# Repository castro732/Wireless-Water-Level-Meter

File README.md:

# Wireless Water Level Meter

## Description

System for measuring the water level in a tank using a current loop (4 mA to 20 mA) wirelessly.

The system consists of 2 modules, a local module and a remote module.
	The local module reads the level of water and transmits it to the remote module (using nRF24L0).
	The remote receives the data and displays it using 5 LEDs, corresponding to the 5 levels of water, from empty to full.

## Features
- Wireless, using nRF24L0.
- Programmed via Arduino using an Atmega328P.
- LEDs indicating the level of water in both modules (local and remote).
- Powered with 5V via screw terminals.
- Programming headers (serial) to facilitate the reprogramming of the microcontrollers.
	- Programs using an Arduino.

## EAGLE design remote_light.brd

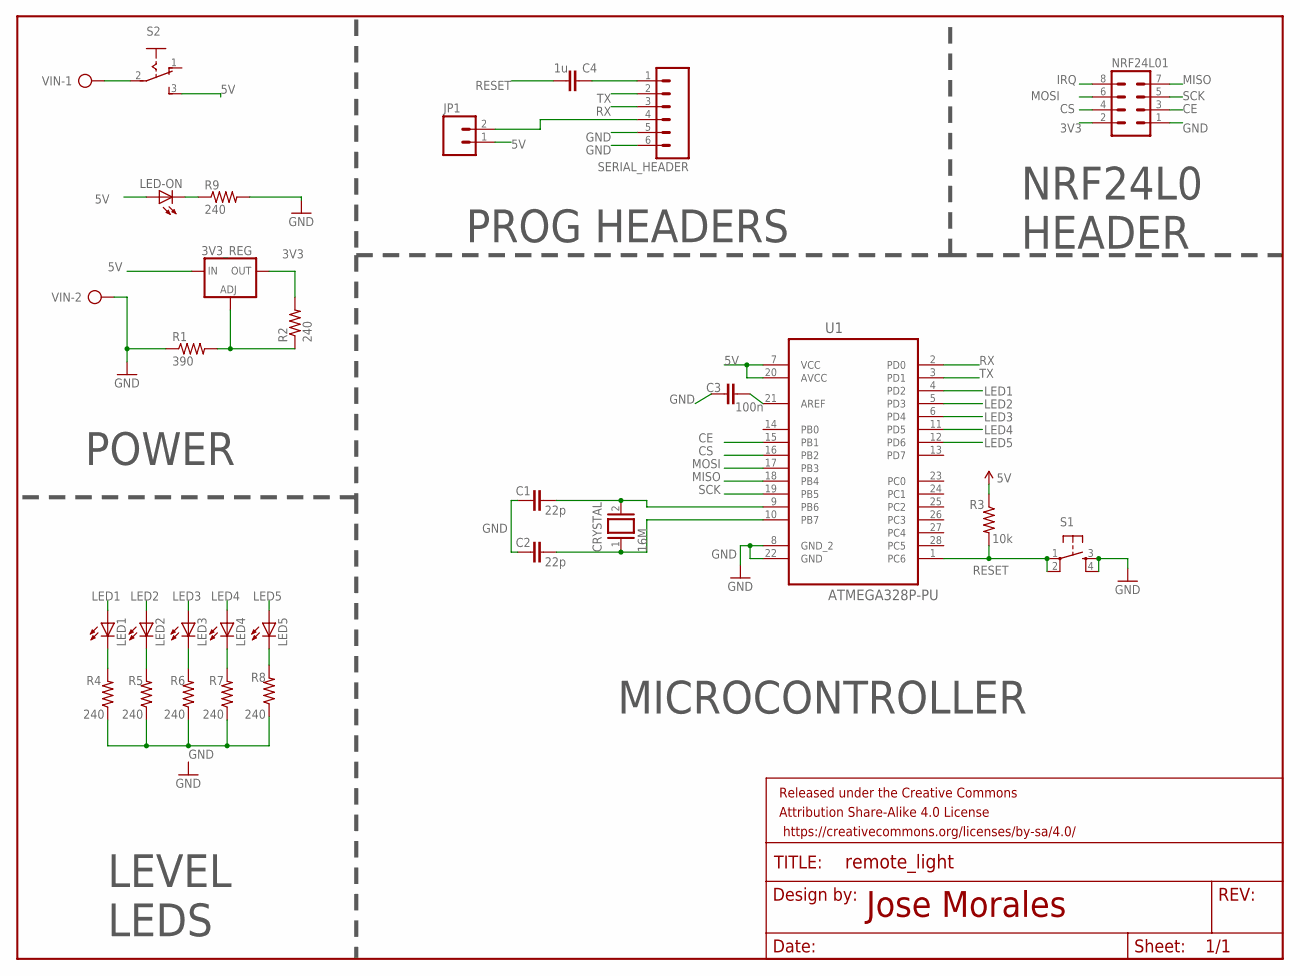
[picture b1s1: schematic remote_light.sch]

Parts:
C1, C2: 22p; C050-025X075
C3: 100n; C050-025X075
C4: 1u; C050-025X075
CRYSTAL: 16M; QS
FRAME11: FRAME-LETTER; CREATIVE_COMMONS
JP1: M02LOCK; 1X02_LOCK
LED1, LED2, LED3, LED4, LED5: LED5MM
LED-ON: LED5MM
LM317: 3V3_REG; 317TS
NRF24L01: MA04-2
R1: 390; 0207/12
R2, R4, R5, R6, R7, R8, R9: 240; 0207/12
R3: 10k; 0207/12
S1: TAC_SWITCHPTH; TACTILE-PTH
S2: 255SB
SERIAL_HEADER: M06POLAR; MOLEX-1X6
U1: ATMEGA328P-PU; DIP254P762X457-28
VIN: AK300/2

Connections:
3V3: LM317.2 (OUT), NRF24L01.2, R2.2
5V: JP1.1, LED-ON.A, LM317.3 (IN), R3.1, S2.3 (S), U1.7 (VCC), U1.20 (AVCC)
CE: NRF24L01.3, U1.15 (PB1)
CS: NRF24L01.4, U1.16 (PB2)
GND: C1.2, C2.2, C3.2, NRF24L01.1, R1.1, R4.1, R5.1, R6.1, R7.1, R8.1, R9.2, S1.3, S1.4, SERIAL_HEADER.5, SERIAL_HEADER.6, U1.8 (GND_2), U1.22 (GND), VIN.2
IRQ: NRF24L01.8
LED1: LED1.A, U1.4 (PD2)
LED2: LED2.A, U1.5 (PD3)
LED3: LED3.A, U1.6 (PD4)
LED4: LED4.A, U1.11 (PD5)
LED5: LED5.A, U1.12 (PD6)
MISO: NRF24L01.7, U1.18 (PB4)
MOSI: NRF24L01.6, U1.17 (PB3)
unnamed: LM317.1 (ADJ), R1.2, R2.1
unnamed: C1.1, CRYSTAL.2, U1.9 (PB6)
unnamed: LED1.K (C), R4.2
unnamed: LED-ON.K (C), R9.1
unnamed: C2.1, CRYSTAL.1, U1.10 (PB7)
unnamed: LED2.K (C), R5.2
unnamed: LED3.K (C), R6.2
unnamed: LED4.K (C), R7.2
unnamed: LED5.K (C), R8.2
unnamed: C3.1, U1.21 (AREF)
unnamed: C4.2, SERIAL_HEADER.1
unnamed: S2.2, VIN.1
unnamed: JP1.2, SERIAL_HEADER.4
RESET: C4.1, R3.2, S1.1, S1.2, U1.1 (PC6)
RX: SERIAL_HEADER.3, U1.2 (PD0)
SCK: NRF24L01.5, U1.19 (PB5)
TX: SERIAL_HEADER.2, U1.3 (PD1)

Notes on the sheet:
Jose Morales
POWER
PROG HEADERS
NRF24L0 HEADER
LEVEL LEDS
MICROCONTROLLER

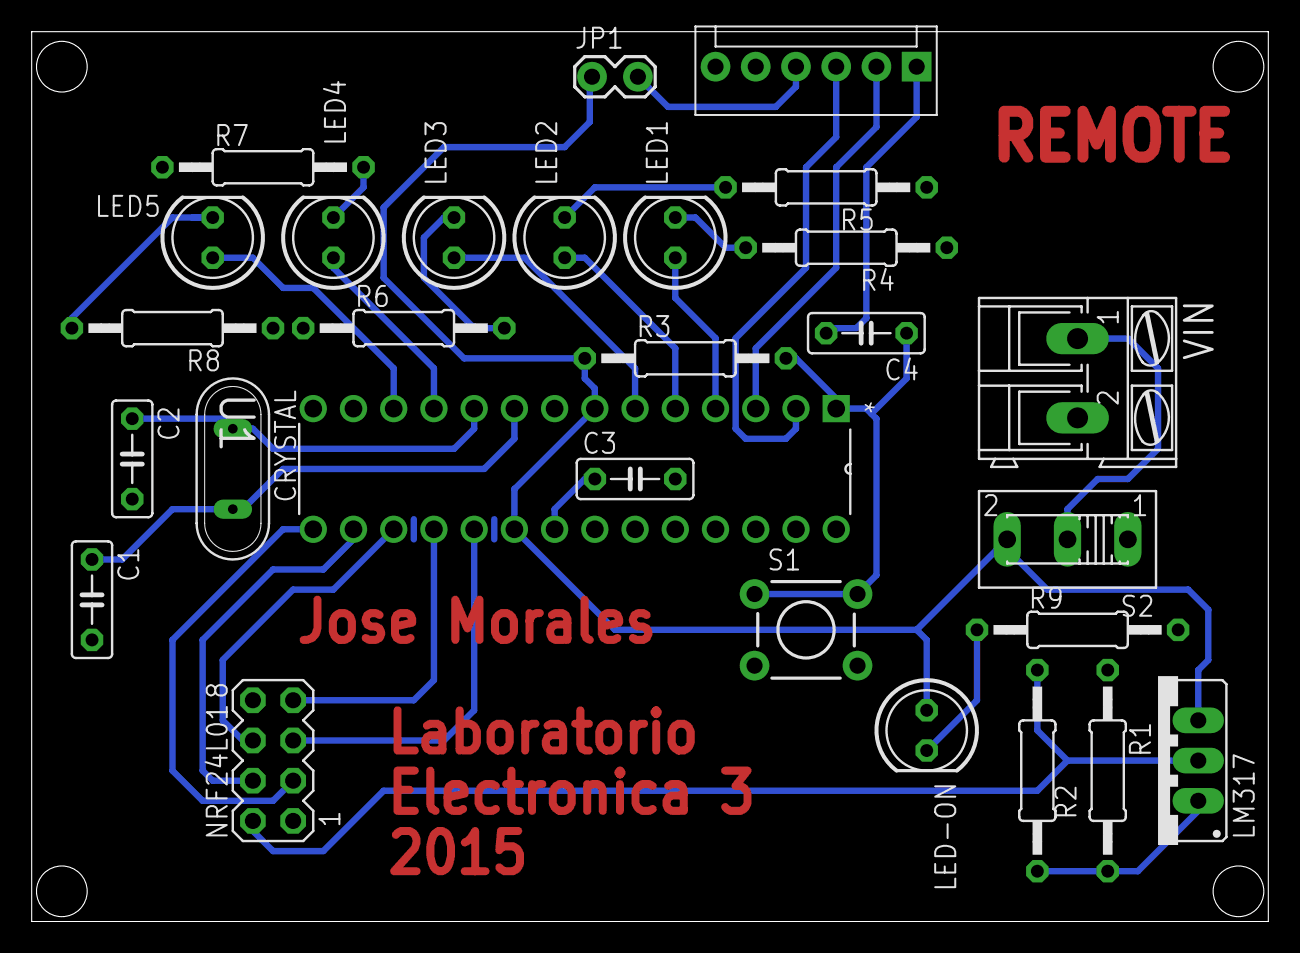
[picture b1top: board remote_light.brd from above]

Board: 2 copper layers, 78.1 x 56.2 mm, 29 parts (0 on the bottom side), 29 nets.

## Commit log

2016-08-07 Add files
2016-08-07 Update built image

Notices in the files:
parts and their libraries:
SparkFun-Retired: Licensing:Creative Commons ShareAlike 4.0 International - https://creativecommons.org/licenses/by-sa/4.0
SparkFun-Aesthetics: Released under the Creative Commons Attribution Share-Alike 4.0 License
SparkFun-Aesthetics: https://creativecommons.org/licenses/by-sa/4.0
